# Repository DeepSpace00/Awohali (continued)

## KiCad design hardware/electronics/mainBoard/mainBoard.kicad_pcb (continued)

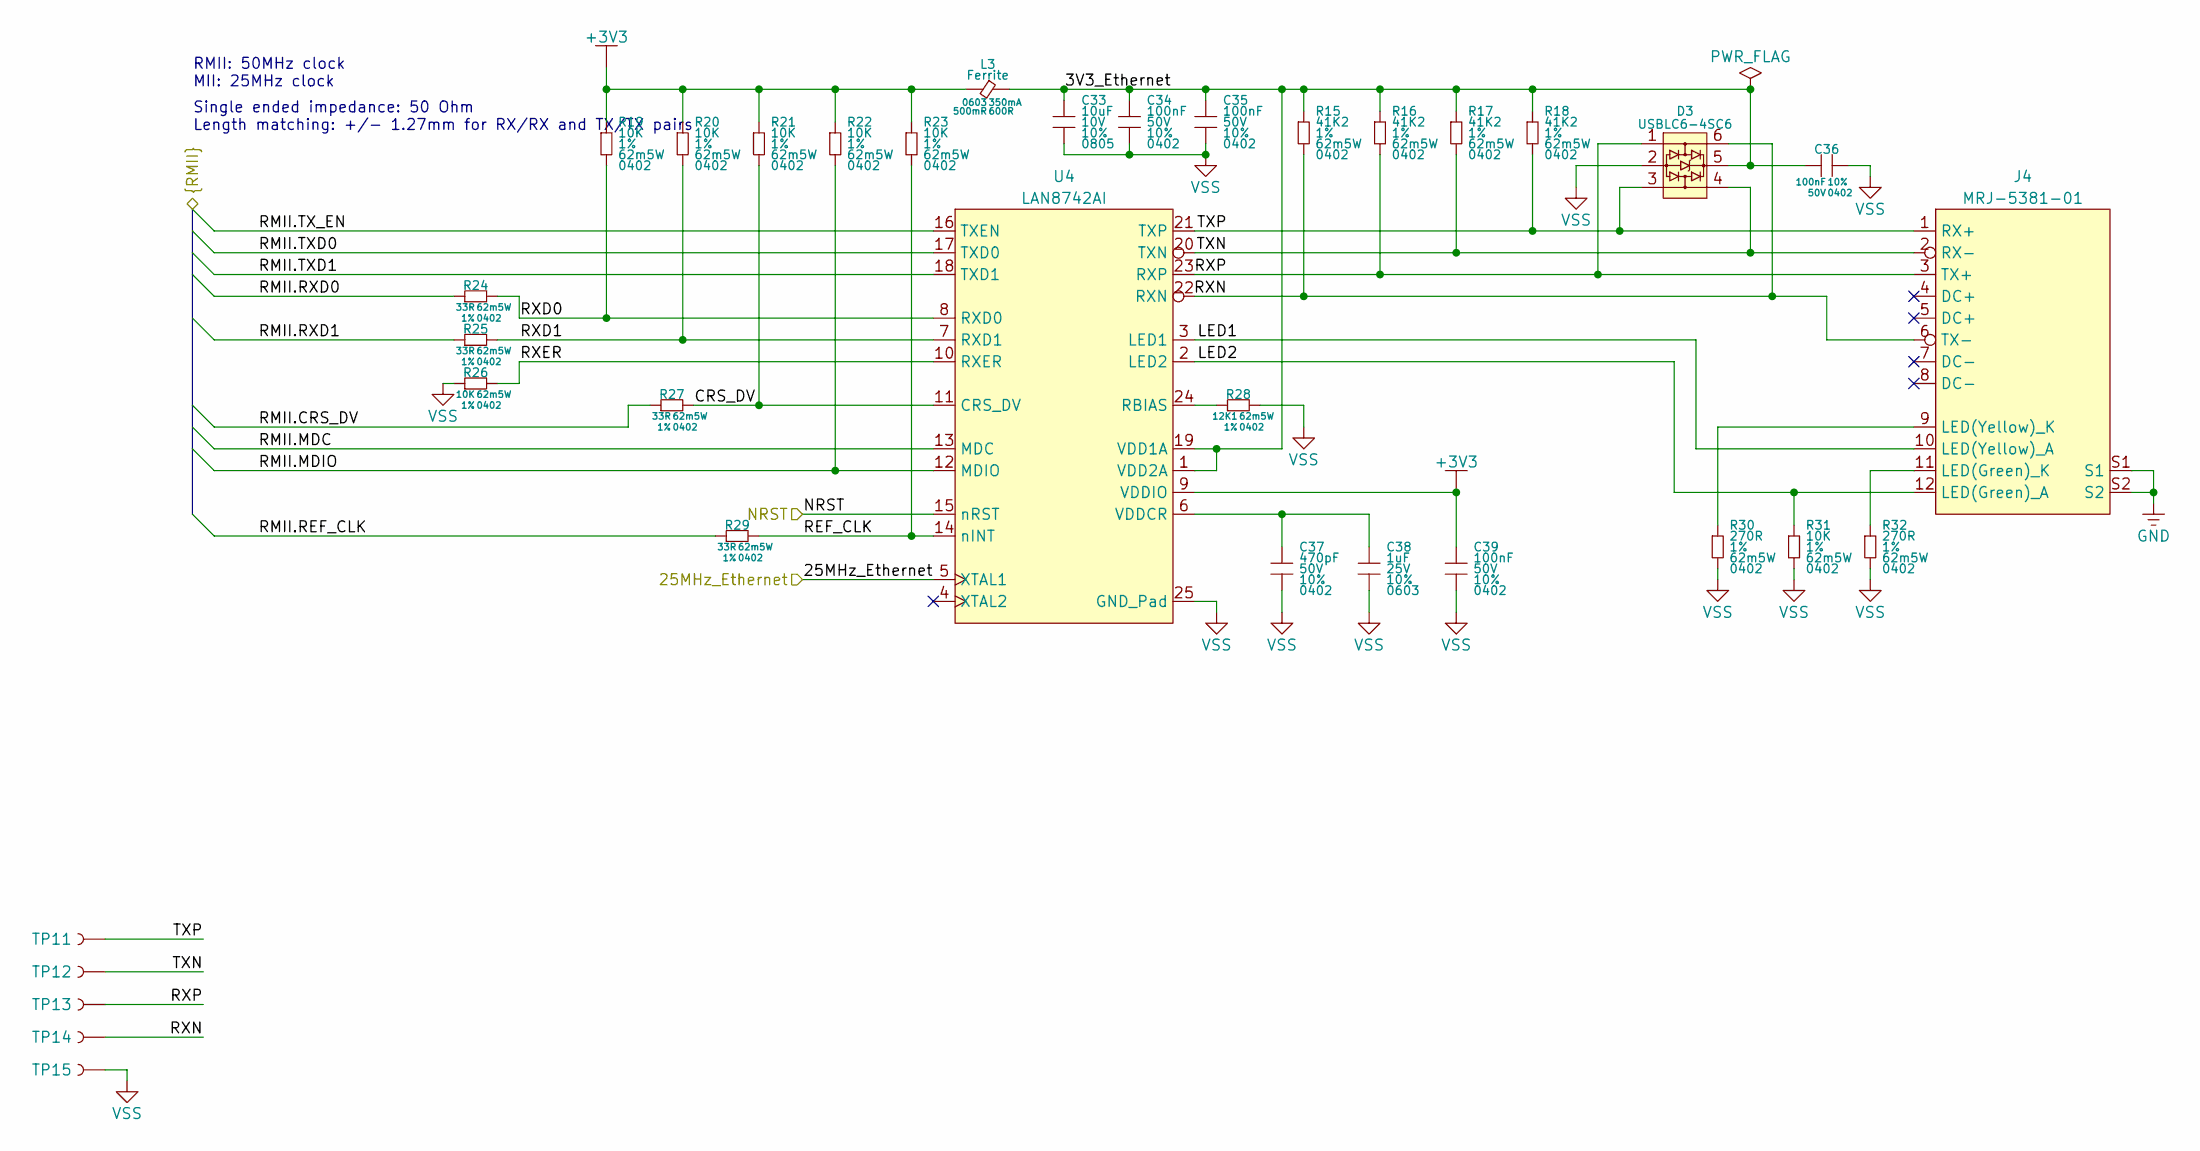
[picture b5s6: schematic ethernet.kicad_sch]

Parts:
C33: 10uF; GCM0805; Tolerance 10%; Voltage Rating 10V; MPN GCM21BR71A106KE22L
C34, C35, C36, C39: 100nF; GCM0402; Tolerance 10%; Voltage Rating 50V; MPN GRT155R71H104KE01D
C37: 470pF; GCM0402; Tolerance 10%; Voltage Rating 50V; MPN GRT155R71H471KE01D
C38: 1uF; GRT0603; Tolerance 10%; Voltage Rating 25V; MPN GRT188R71E105KE13D
D3: USBLC6-4SC6; SOT2395P280X145-6; MPN USBLC6-4SC6
J4: MRJ-5381-01; MJR-5381-X1; MPN MRJ-5381-01
L3: Ferrite; L_0603; Current Rating 350mA; MPN MFBA3V1608K-601-R
R15, R16, R17, R18: 41K2; CRCW0402; Tolerance 1%; Power Rating 62m5W; MPN CRCW040241R2FKED
R19, R20, R21, R22, R23, R26, R31: 10K; CRCW0402; Tolerance 1%; Power Rating 62m5W; MPN CRCW040210K0FKED
R24, R25, R27, R29: 33R; CRCW0402; Tolerance 1%; Power Rating 62m5W; MPN CRCW040233R0FKED
R28: 12K1; CRCW0402; Tolerance 1%; Power Rating 62m5W; MPN CRCW040212K1FKED
R30, R32: 270R; CRCW0402; Tolerance 1%; Power Rating 62m5W; MPN CRCW0402270RFKED
TP11, TP12, TP13, TP14: TP_2mm; MPN N/A
TP15: RCWCTE; TP_RCW; MPN RCWCTE
U4: LAN8742AI; QFN50P400X400X90-24; MPN LAN8742AI-CZ-TR

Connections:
+3V3: C39.1, L3.1, R19.1, R20.1, R21.1, R22.1, R23.1, U4.9 (VDDIO); also elsewhere on the board
/Ethernet/3V3_Ethernet: C33.1, C34.1, C35.1, C36.1, D3.5 (VBUS), L3.2, R15.1, R16.1, R17.1, R18.1, U4.1 (VDD2A), U4.19 (VDD1A)
/Ethernet/25MHz_Ethernet: U4.5 (XTAL1); also elsewhere on the board
/Ethernet/CRS_DV: R21.2, R27.2, U4.11 (CRS_DV)
/Ethernet/LED1: J4.10 (LED(Yellow)_A), U4.3 (LED1)
/Ethernet/LED2: J4.12 (LED(Green)_A), R31.1, U4.2 (LED2)
/Ethernet/REF_CLK: R23.2, R29.2, U4.14 (nINT)
/Ethernet/RMII.CRS_DV: R27.1; also elsewhere on the board
/Ethernet/RMII.MDC: U4.13 (MDC); also elsewhere on the board
/Ethernet/RMII.MDIO: R22.2, U4.12 (MDIO); also elsewhere on the board
/Ethernet/RMII.REF_CLK: R29.1; also elsewhere on the board
/Ethernet/RMII.RXD0: R24.1; also elsewhere on the board
/Ethernet/RMII.RXD1: R25.1; also elsewhere on the board
/Ethernet/RMII.TXD0: U4.17 (TXD0); also elsewhere on the board
/Ethernet/RMII.TXD1: U4.18 (TXD1); also elsewhere on the board
/Ethernet/RMII.TX_EN: U4.16 (TXEN); also elsewhere on the board
/Ethernet/RXD0: R19.2, R24.2, U4.8 (RXD0)
/Ethernet/RXD1: R20.2, R25.2, U4.7 (RXD1)
/Ethernet/RXER: R26.2, U4.10 (RXER)
/Ethernet/RXN: D3.6 (OUT1), J4.6 (TX-), R15.2, TP14.1, U4.22 (RXN)
/Ethernet/RXP: D3.1 (IN1), J4.3 (TX+), R16.2, TP13.1, U4.23 (RXP)
/Ethernet/TXN: D3.4 (OUT2), J4.2 (RX-), R17.2, TP12.1, U4.20 (TXN)
/Ethernet/TXP: D3.3 (IN2), J4.1 (RX+), R18.2, TP11.1, U4.21 (TXP)
/H7_NRST: U4.15 (nRST); also elsewhere on the board
GND: J4.S1, J4.S2; also elsewhere on the board
unnamed: J4.11 (LED(Green)_K), R32.1
unnamed: J4.9 (LED(Yellow)_K), R30.1
unnamed: R28.1, U4.24 (RBIAS)
unnamed: C37.1, C38.1, U4.6 (VDDCR)
VSS: C33.2, C34.2, C35.2, C36.2, C37.2, C38.2, C39.2, D3.2 (GND), R26.1, R28.2, R30.2, R31.2, R32.2, TP15.1, U4.25 (GND_Pad); also elsewhere on the board

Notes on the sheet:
RMII: 50MHz clock MII: 25MHz clock
Single ended impedance: 50 Ohm Length matching: +/- 1.27mm for RX/RX and TX/TX pairs

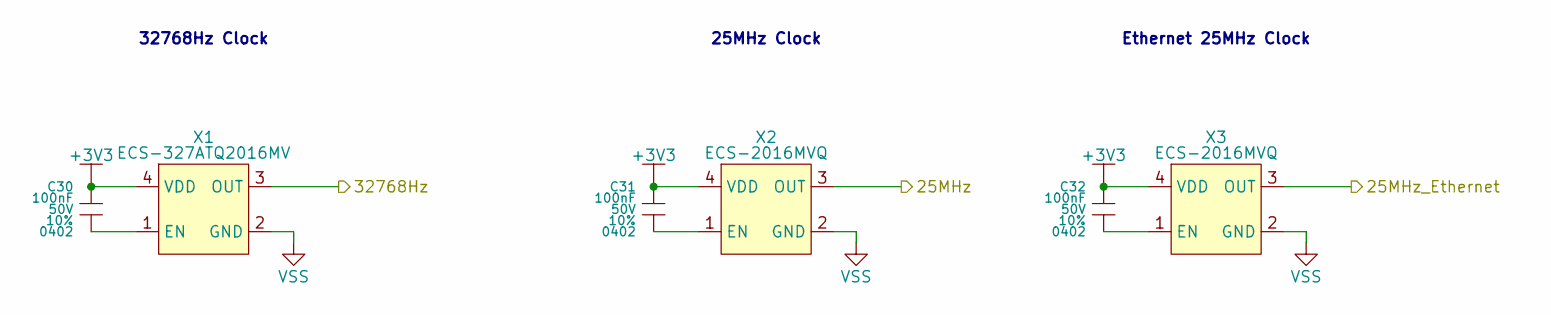
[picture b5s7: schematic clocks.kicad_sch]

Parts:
C30, C31, C32: 100nF; GCM0402; Tolerance 10%; Voltage Rating 50V; MPN GRT155R71H104KE01D
X1: ECS-327ATQ2016MV; ECS-xxxATQ2016MV; MPN ECS-327ATQ2016MV-BS-TR
X2, X3: ECS-2016MVQ; ECS-2016MV; MPN ECS-2016MVQ-250-CN-TR

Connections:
+3V3: C30.1, C31.1, C32.1, X1.4 (VDD), X2.4 (VDD), X3.4 (VDD); also elsewhere on the board
/Ethernet/25MHz_Ethernet: X3.3 (OUT); also elsewhere on the board
/STM32H745/25MHz: X2.3 (OUT); also elsewhere on the board
/STM32H745/32768Hz: X1.3 (OUT); also elsewhere on the board
unnamed: C30.2, X1.1 (EN)
unnamed: C31.2, X2.1 (EN)
unnamed: C32.2, X3.1 (EN)
VSS: X1.2 (GND), X2.2 (GND), X3.2 (GND); also elsewhere on the board

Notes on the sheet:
25MHz Clock
32768Hz Clock
Ethernet 25MHz Clock

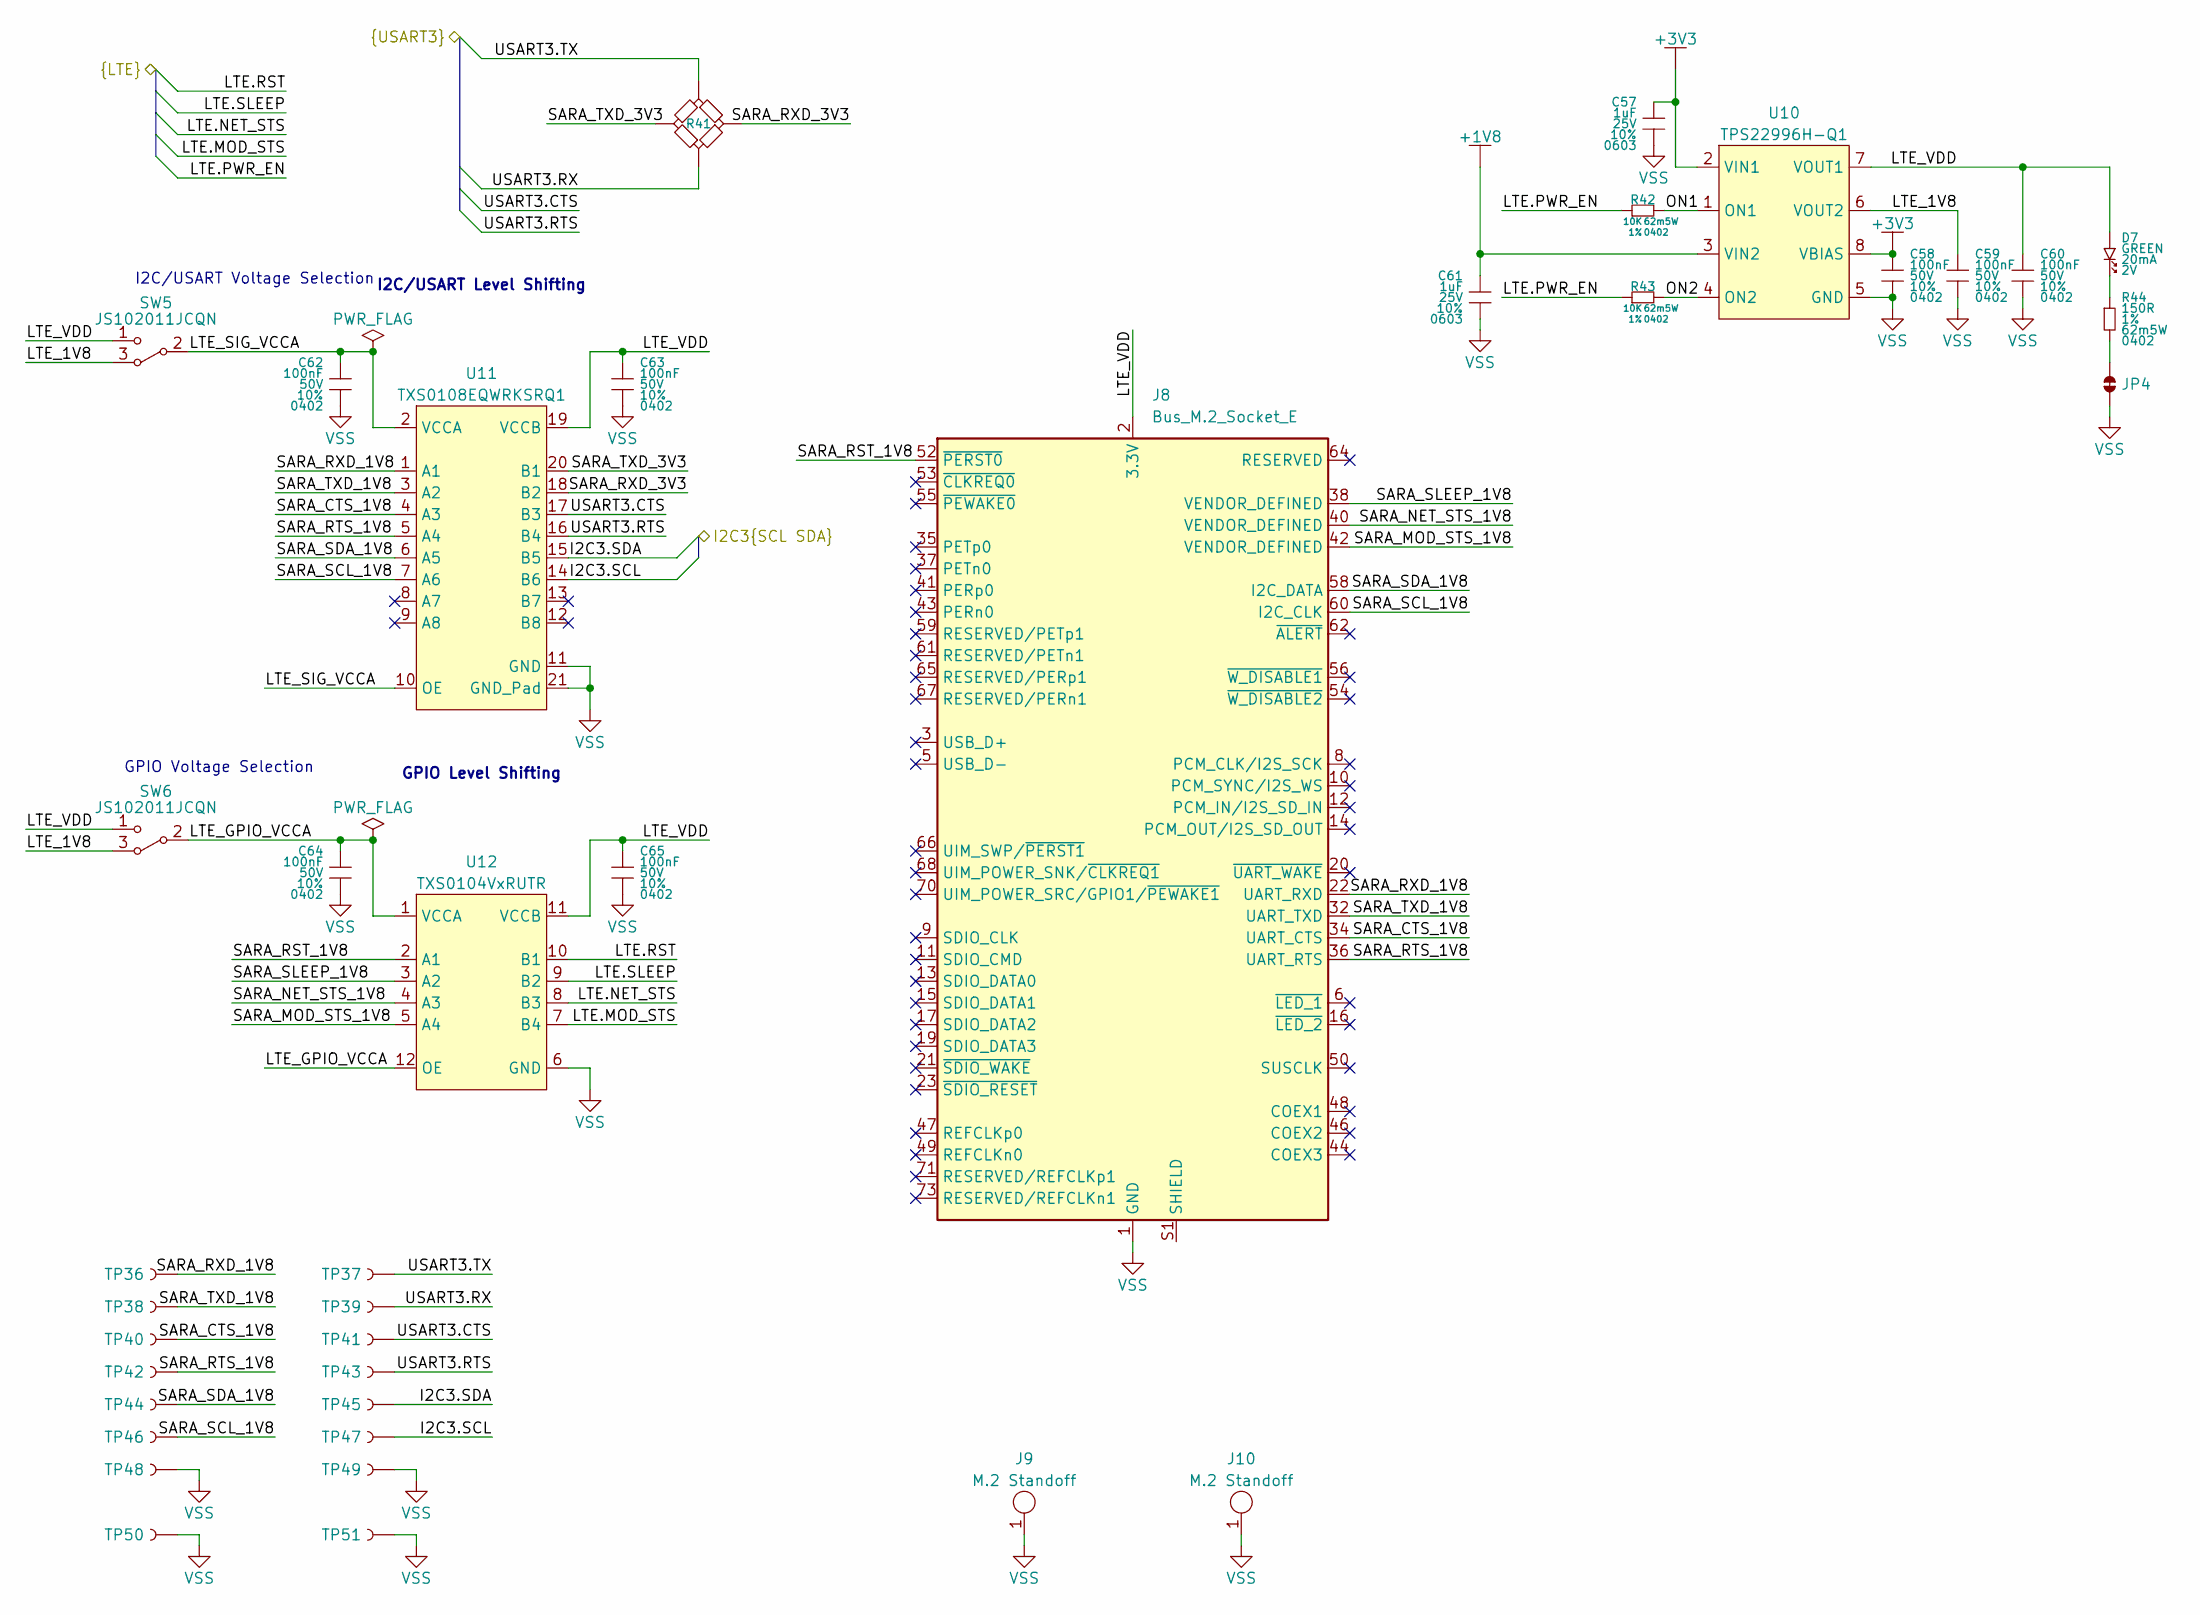
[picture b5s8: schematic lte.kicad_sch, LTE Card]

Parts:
C57, C61: 1uF; GRT0603; Tolerance 10%; Voltage Rating 25V; MPN GRT188R71E105KE13D
C58, C59, C60, C62, C63, C64, C65: 100nF; GCM0402; Tolerance 10%; Voltage Rating 50V; MPN GRT155R71H104KE01D
D7: LTST-C191KGKT; LTST-0603; Forward Voltage 2V; MPN LTST-C191KGKT
J8: Bus_M.2_Socket_E; MDT420E01001; MPN MDT420E01001
J9, J10: M.2 Standoff; MountingHole_3.5mm_Pad_Via; MPN 123A-NUT-42
JP4: SolderJumper-2_P1.3mm_Bridged_RoundedPad1.0x1.5mm
R41: CRCW0402_QUAD_UART
R42, R43: 10K; CRCW0402; Tolerance 1%; Power Rating 62m5W; MPN CRCW040210K0FKED
R44: 150R; CRCW0402; Tolerance 1%; Power Rating 62m5W; MPN CRCW0402150RFKED
SW5, SW6: JS102011JCQN; MPN C&K
TP36, TP37, TP38, TP39, TP40, TP41, TP42, TP43, TP44, TP45, TP46, TP47: TP_2mm; MPN N/A
TP48, TP49, TP50, TP51: RCWCTE; TP_RCW; MPN RCWCTE
U10: TPS22996H-Q1; SOT583; MPN TPS22996HQDYCRQ1
U11: TXS0108EQWRKSRQ1; QFN50P450X250X100-20; MPN TXS0108EQWRKSRQ1
U12: TXS0104VxRUTR; QFN40P170X200X55-12; MPN TXS0104VQRUTRQ1

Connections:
+1V8: C61.1, U10.3 (VIN2); also elsewhere on the board
+3V3: C57.1, C58.1, U10.2 (VIN1), U10.8 (VBIAS); also elsewhere on the board
/I2C3.SCL: TP47.1, U11.14 (B6); also elsewhere on the board
/I2C3.SDA: TP45.1, U11.15 (B5); also elsewhere on the board
/LTE Card/LTE.MOD_STS: U12.7 (B4); also elsewhere on the board
/LTE Card/LTE.NET_STS: U12.8 (B3); also elsewhere on the board
/LTE Card/LTE.PWR_EN: R42.1, R43.1; also elsewhere on the board
/LTE Card/LTE.RST: U12.10 (B1); also elsewhere on the board
/LTE Card/LTE.SLEEP: U12.9 (B2); also elsewhere on the board
/LTE Card/LTE_1V8: C59.1, SW5.3, SW6.3, U10.6 (VOUT2)
/LTE Card/LTE_GPIO_VCCA: C64.1, SW6.2, U12.1 (VCCA), U12.12 (OE)
/LTE Card/LTE_SIG_VCCA: C62.1, SW5.2, U11.2 (VCCA), U11.10 (OE)
/LTE Card/LTE_VDD: C60.1, C63.1, C65.1, D7.1, J8.2 (3.3V), J8.4 (3.3V), J8.72 (3.3V), J8.74 (3.3V), SW5.1, SW6.1, U10.7 (VOUT1), U11.19 (VCCB), U12.11 (VCCB)
/LTE Card/ON1: R42.2, U10.1 (ON1)
/LTE Card/ON2: R43.2, U10.4 (ON2)
/LTE Card/SARA_CTS_1V8: J8.34 (UART_CTS), TP40.1, U11.4 (A3)
/LTE Card/SARA_MOD_STS_1V8: J8.42 (VENDOR_DEFINED), U12.5 (A4)
/LTE Card/SARA_NET_STS_1V8: J8.40 (VENDOR_DEFINED), U12.4 (A3)
/LTE Card/SARA_RST_1V8: J8.52 (~PERST0), U12.2 (A1)
/LTE Card/SARA_RTS_1V8: J8.36 (UART_RTS), TP42.1, U11.5 (A4)
/LTE Card/SARA_RXD_1V8: J8.22 (UART_RXD), TP36.1, U11.1 (A1)
/LTE Card/SARA_RXD_3V3: R41.2, U11.18 (B2)
/LTE Card/SARA_SCL_1V8: J8.60 (I2C_CLK), TP46.1, U11.7 (A6)
/LTE Card/SARA_SDA_1V8: J8.58 (I2C_DATA), TP44.1, U11.6 (A5)
/LTE Card/SARA_SLEEP_1V8: J8.38 (VENDOR_DEFINED), U12.3 (A2)
/LTE Card/SARA_TXD_1V8: J8.32 (UART_TXD), TP38.1, U11.3 (A2)
/LTE Card/SARA_TXD_3V3: R41.4, U11.20 (B1)
/LTE Card/USART3.CTS: TP41.1, U11.17 (B3); also elsewhere on the board
/LTE Card/USART3.RTS: TP43.1, U11.16 (B4); also elsewhere on the board
/LTE Card/USART3.RX: R41.3, TP39.1; also elsewhere on the board
/LTE Card/USART3.TX: R41.1, TP37.1; also elsewhere on the board
unnamed: D7.2, R44.1
unnamed: J8.S1 (SHIELD), J8.S2 (SHIELD)
unnamed: JP4.1, R44.2
VSS: C57.2, C58.2, C59.2, C60.2, C61.2, C62.2, C63.2, C64.2, C65.2, J8.1 (GND), J8.7 (GND), J8.18 (GND), J8.33 (GND), J8.39 (GND), J8.45 (GND), J8.51 (GND), J8.57 (GND), J8.63 (GND), J8.69 (GND), J8.75 (GND), J9.1, J10.1, JP4.2, TP48.1, TP49.1, TP50.1, TP51.1, U10.5 (GND), U11.11 (GND), U11.21 (GND_Pad), U12.6 (GND); also elsewhere on the board

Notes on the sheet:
I2C/USART Voltage Selection
I2C/USART Level Shifting
GPIO Voltage Selection
GPIO Level Shifting

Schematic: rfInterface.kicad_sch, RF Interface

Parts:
AE1: TNC; RFPC-TNC01-FN; MPN RFPC-TNC01-FN-A
AE2: SMA; RFPC-SMA14-FN; MPN RFPC-SMA14-FN-A
AE3: SMA; RFPC-SMA14-FN; MPN RFPC-SMA14-FN-A; not fitted
C75, C76: 100nF; GCM0402; Tolerance 10%; Voltage Rating 50V; MPN GRT155R71H104KE01D
C77, C79: 9.1pF; GCM0402; Tolerance 0.1pF; Voltage Rating 50V; MPN GCM1555C1H9R1BA16D
C78: 5.6pF; GCM0402; Tolerance 0.1pF; Voltage Rating 50V; MPN GCM1555C1H5R6BA16D
C80, C81: 100pF; GCM0402; Tolerance 1%; Voltage Rating 50V; MPN GCM1555C1H101FA16D
J14, J15, J16, J17: CONMHF1-SMD-T; CONMHF1; MPN CONMHF1-SMD-T
L4: 15nH; L_0402; Tolerance 2%; Current Rating 1A15; MPN LQW15AN15NG8ZD
L5: 6.8nH; L_0402; Tolerance 2%; Current Rating 1A45; MPN LQW15AN6N8G8ZD
R53: 750R; CRCW0402; Tolerance 1%; Power Rating 62m5W; MPN CRCW0402750RFKED
R54: 267R; CRCW0402; Tolerance 1%; Power Rating 62m5W; MPN CRCW0402267RFKED
R55: 49R9; CRCW0402; Tolerance 1%; Power Rating 62m5W; MPN CRCW040249R9FKED
U16: PMA2-162LNA+; TFDFN200X200X100-8; MPN PMA2-162LNA+
U17: QCN-19D+; SON99P320X160X89-6; MPN QCN-19D+

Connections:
/RF Interface/AUX_RF-IN: AE3.1 (A), J17.1 (In)
/RF Interface/GNSS_CONN1: J14.1 (In), U17.4 (PORT1)
/RF Interface/GNSS_CONN2: J15.1 (In), U17.6 (PORT2)
/RF Interface/GNSS_RF-IN: AE1.1 (A), C79.1
/RF Interface/LNA_BIAS: R53.2, U16.4 (BIAS)
/RF Interface/LNA_FB: C78.1, U16.5 (FB)
/RF Interface/LNA_RBIAS: C75.1, C76.1, C77.1, L4.1, R53.1
/RF Interface/LNA_RF-GND: C81.1, L5.2, U16.3 (RF-GND)
/RF Interface/LNA_RF-IN: C79.2, L5.1, U16.2 (RF-IN)
/RF Interface/LNA_RF-OUT: C80.1, L4.2, R54.2, U16.7 (RF-OUT)
/RF Interface/LTE_RF-IN: AE2.1 (A), J16.1 (In)
/RF Interface/RF-SPLIT_50R: R55.1, U17.3 (50R)
/RF Interface/RF-SPLIT_SUM: C80.2, U17.1 (SUM)
unnamed: C78.2, R54.1
VSS: AE1.2 (Shield), AE1.3 (Shield), AE1.4 (Shield), AE1.5 (Shield), AE2.2 (Shield), AE2.3 (Shield), AE2.4 (Shield), AE2.5 (Shield), AE3.2 (Shield), AE3.3 (Shield), AE3.4 (Shield), AE3.5 (Shield), C75.2, C76.2, C77.2, C81.2, J14.2 (Ext), J15.2 (Ext), J16.2 (Ext), J17.2 (Ext), R55.2, U16.1 (NC), U16.6 (NC), U16.8 (GND), U16.9 (GND), U17.2 (GND), U17.5 (GND); also elsewhere on the board

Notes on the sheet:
GNSS Card Cable
LTE Card Cable
Single ended impedance: 50 Ohms
AUX Card Cable

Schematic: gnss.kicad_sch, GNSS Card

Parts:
C48, C52: 1uF; GRT0603; Tolerance 10%; Voltage Rating 25V; MPN GRT188R71E105KE13D
C49, C50, C51, C53, C54, C55, C56: 100nF; GCM0402; Tolerance 10%; Voltage Rating 50V; MPN GRT155R71H104KE01D
D4: LTST-C191KGKT; LTST-0603; Forward Voltage 2V; MPN LTST-C191KGKT
J5: Bus_M.2_Socket_E; MDT420E01001; MPN MDT420E01001
J6, J7: M.2 Standoff; MountingHole_3.5mm_Pad_Via; MPN 123A-NUT-42
JP1: SolderJumper-2_P1.3mm_Bridged_RoundedPad1.0x1.5mm
R35: CRCW0402_QUAD_UART
R36, R37: 10K; CRCW0402; Tolerance 1%; Power Rating 62m5W; MPN CRCW040210K0FKED
R38: 150R; CRCW0402; Tolerance 1%; Power Rating 62m5W; MPN CRCW0402150RFKED
SW3, SW4: JS102011JCQN; MPN C&K
TP24, TP25, TP26, TP27, TP28, TP29, TP30, TP31: TP_2mm; MPN N/A
TP32, TP33, TP34, TP35: RCWCTE; TP_RCW; MPN RCWCTE
U7: TPS22996H-Q1; SOT583; MPN TPS22996HQDYCRQ1
U8, U9: TXS0104VxRUTR; QFN40P170X200X55-12; MPN TXS0104VQRUTRQ1

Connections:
+1V8: C52.1, U7.3 (VIN2); also elsewhere on the board
+3V3: C48.1, C49.1, U7.2 (VIN1), U7.8 (VBIAS); also elsewhere on the board
/GNSS Card/GNSS.INT: U9.9 (B2); also elsewhere on the board
/GNSS Card/GNSS.PPS: U9.10 (B1); also elsewhere on the board
/GNSS Card/GNSS.PWR_EN: R36.1, R37.1; also elsewhere on the board
/GNSS Card/GNSS.RST: J5.52 (~PERST0); also elsewhere on the board
/GNSS Card/GNSS.TX_RDY: U9.8 (B3); also elsewhere on the board
/GNSS Card/GNSS_1V8: C50.1, SW3.3, SW4.3, U7.6 (VOUT2)
/GNSS Card/GNSS_VDD: C51.1, C54.1, C56.1, D4.1, J5.2 (3.3V), J5.4 (3.3V), J5.72 (3.3V), J5.74 (3.3V), SW3.1, SW4.1, U7.7 (VOUT1), U8.11 (VCCB), U9.11 (VCCB)
/GNSS Card/GPS_GPIO_VCCA: C55.1, SW4.2, U9.1 (VCCA), U9.12 (OE)
/GNSS Card/GPS_SIG_VCCA: C53.1, SW3.2, U8.1 (VCCA), U8.12 (OE)
/GNSS Card/ON1: R36.2, U7.1 (ON1)
/GNSS Card/ON2: R37.2, U7.4 (ON2)
/GNSS Card/UART5.RX: R35.1, TP25.1; also elsewhere on the board
/GNSS Card/UART5.TX: R35.3, TP27.1; also elsewhere on the board
/GNSS Card/ZED_INT: J5.40 (VENDOR_DEFINED), U9.3 (A2)
/GNSS Card/ZED_PPS: J5.38 (VENDOR_DEFINED), U9.2 (A1)
/GNSS Card/ZED_RXD_1V8: J5.22 (UART_RXD), TP26.1, U8.3 (A2)
/GNSS Card/ZED_RXD_3V3: R35.2, U8.9 (B2)
/GNSS Card/ZED_SCL_1V8: J5.60 (I2C_CLK), TP30.1, U8.5 (A4)
/GNSS Card/ZED_SDA_1V8: J5.58 (I2C_DATA), TP28.1, U8.4 (A3)
/GNSS Card/ZED_TXD_1V8: J5.32 (UART_TXD), TP24.1, U8.2 (A1)
/GNSS Card/ZED_TXD_3V3: R35.4, U8.10 (B1)
/GNSS Card/ZED_TX_RDY: J5.42 (VENDOR_DEFINED), U9.4 (A3)
/I2C2.SCL: TP31.1, U8.7 (B4); also elsewhere on the board
/I2C2.SDA: TP29.1, U8.8 (B3); also elsewhere on the board
unnamed: D4.2, R38.1
unnamed: JP1.1, R38.2
VSS: C48.2, C49.2, C50.2, C51.2, C52.2, C53.2, C54.2, C55.2, C56.2, J5.1 (GND), J5.7 (GND), J5.18 (GND), J5.33 (GND), J5.39 (GND), J5.45 (GND), J5.51 (GND), J5.57 (GND), J5.63 (GND), J5.69 (GND), J5.75 (GND), J5.S1 (SHIELD), J5.S2 (SHIELD), J6.1, J7.1, JP1.2, TP32.1, TP33.1, TP34.1, TP35.1, U7.5 (GND), U8.6 (GND), U9.6 (GND); also elsewhere on the board

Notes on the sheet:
I2C/UART Voltage Selection
GPIO Level Shifting
GNSS Receiver GPIO
GPIO Voltage Selection
I2C/UART Level Shifting

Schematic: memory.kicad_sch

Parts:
C27, C28, C29: 100nF; GCM0402; Tolerance 10%; Voltage Rating 50V; MPN GRT155R71H104KE01D
J3: MEM2067-02-180-00-A; MPN MEM2067-02-180-00-A
TP1, TP2, TP3, TP4, TP5, TP6, TP7, TP8: TP_2mm; MPN N/A
TP9, TP10: RCWCTE; TP_RCW; MPN RCWCTE
U2: W25Q128JVP; WFDFN8P127_600X500X75L60X40N; MPN W25Q128JVPIQ
U3: M24512-DRE; SOIC127P600x175-8; MPN M24512-DRMN8TP/K

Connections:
+3V3: C27.1, C28.1, C29.1, J3.4 (VDD), U2.8 (VCC), U3.8 (VCC); also elsewhere on the board
/I2C1.SCL: TP1.1, U3.6 (SCL); also elsewhere on the board
/I2C1.SDA: TP2.1, U3.5 (SDA); also elsewhere on the board
/Memory/EEPROM_WC: U3.7 (~WC); also elsewhere on the board
/Memory/QSPI1.CLK: TP4.1, U2.6 (SCK); also elsewhere on the board
/Memory/QSPI1.IO0: TP5.1, U2.5 (IO0); also elsewhere on the board
/Memory/QSPI1.IO1: TP6.1, U2.2 (IO1); also elsewhere on the board
/Memory/QSPI1.IO2: TP7.1, U2.3 (IO2); also elsewhere on the board
/Memory/QSPI1.IO3: TP8.1, U2.7 (IO3); also elsewhere on the board
/Memory/QSPI1.NCS: TP3.1, U2.1 (~CS); also elsewhere on the board
/Memory/SDMMC2.CLK: J3.5 (CLK); also elsewhere on the board
/Memory/SDMMC2.CMD: J3.3 (CMD); also elsewhere on the board
/Memory/SDMMC2.D0: J3.7 (DAT0); also elsewhere on the board
/Memory/SDMMC2.D1: J3.8 (DAT1); also elsewhere on the board
/Memory/SDMMC2.D2: J3.1 (DAT2); also elsewhere on the board
/Memory/SDMMC2.D3: J3.2 (DAT3/CD); also elsewhere on the board
VSS: C27.2, C28.2, C29.2, J3.6 (VSS), J3.S1 (SHIELD), J3.S2 (SHIELD), J3.S3 (SHIELD), J3.S4 (SHIELD), TP9.1, TP10.1, U2.4 (GND), U2.9 (GND_PAD), U3.1 (E0), U3.2 (E1), U3.3 (E2), U3.4 (VSS); also elsewhere on the board

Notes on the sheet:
I2C Address: 0x50/0x58

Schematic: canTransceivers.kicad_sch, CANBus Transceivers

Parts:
C40, C41, C44, C45: 1uF; GRT0603; Tolerance 10%; Voltage Rating 25V; MPN GRT188R71E105KE13D
C42, C43, C46, C47: 100nF; GCM0402; Tolerance 10%; Voltage Rating 50V; MPN GRT155R71H104KE01D
R33, R34: 120R; CRCW0402; Tolerance 1%; Power Rating 62m5W; MPN CRCW0402120RFKED
TP16, TP17, TP18, TP19, TP20, TP21: TP_2mm; MPN N/A
TP22, TP23: RCWCTE; TP_RCW; MPN RCWCTE
U5, U6: TCAN3403-Q1; SON65P300X300X100-8; MPN TCAN3403DRBRQ1

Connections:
+3V3: C40.1, C41.1, C42.1, C43.1, C44.1, C45.1, C46.1, C47.1, U5.3 (VCC), U5.5 (VDDIO), U6.3 (VCC), U6.5 (VDDIO); also elsewhere on the board
/CANBus Transceivers/CANH: R33.1, R34.1, TP18.1, U5.7 (CANH), U6.7 (CANH)
/CANBus Transceivers/CANL: R33.2, R34.2, TP19.1, U5.6 (CANL), U6.6 (CANL)
/CANBus Transceivers/FDCAN1_RX: TP17.1, U5.4 (RXD); also elsewhere on the board
/CANBus Transceivers/FDCAN1_TX: TP16.1, U5.1 (TXD); also elsewhere on the board
/CANBus Transceivers/H7_CAN_STB: U5.8 (STB); also elsewhere on the board
/CAN_RXD: TP21.1, U6.4 (RXD); also elsewhere on the board
/CAN_STB: U6.8 (STB); also elsewhere on the board
/CAN_TXD: TP20.1, U6.1 (TXD); also elsewhere on the board
VSS: C40.2, C41.2, C42.2, C43.2, C44.2, C45.2, C46.2, C47.2, TP22.1, TP23.1, U5.2 (GND), U5.9 (GND_PAD), U6.2 (GND), U6.9 (GND_PAD); also elsewhere on the board

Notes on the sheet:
EPS CANBus Transceiver
Host CANBus Transceiver

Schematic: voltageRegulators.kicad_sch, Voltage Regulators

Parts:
C124, C130: 100nF; GCM0402; Tolerance 10%; Voltage Rating 50V; MPN GRT155R71H104KE01D
C125: 4.7uF; GCM0805; Tolerance 10%; Voltage Rating 16V; MPN GRT21BR71C475KE13L
C126, C127, C128, C134: 22uF; GCM1206; Tolerance 20%; Voltage Rating 10V; MPN GCM31CR71A226ME02L
C129: 2.2uF; GCM0805; Tolerance 10%; Voltage Rating 25V; MPN GRT21BR71E225KE13L
C131: 150pF; GCM0402; Tolerance 1%; Voltage Rating 50V; MPN GCM1555C1H151FA16J
C132: 3.9nF; GCM0402; Tolerance 10%; Voltage Rating 50V; MPN GCM155R71H392KA37D
C133: 10uF; GCM0805; Tolerance 10%; Voltage Rating 10V; MPN GCM21BR71A106KE22L
D21, D22: LTST-C191KRKT; LTST-0603; Forward Voltage 2V; MPN LTST-C191KRKT
J30, J31: Conn_01x04_Pin; conn_01x04_254; MPN PRPC004SAAN-RC
JP11, JP13: SolderJumper-2_P1.3mm_Bridged_RoundedPad1.0x1.5mm
JP12: SolderJumper-3_P1.3mm_Bridged12_RoundedPad1.0x1.5mm
L7: 6.8uH; WE-XHMI-1090; Tolerance 20%; Current Rating 10A5; MPN 74439369068
L8: 1uH; WE-XHMI-8080; Tolerance 20%; Current Rating 17A; MPN 74439358010
Q8, Q9: CSD17581Q3A; SON65P300X315X90-8; MPN CSD17581Q3A
Q10, Q11: BSS138-7-F; SOT23; MPN BSS138-7-F
R83, R90: 150R; CRCW0402; Tolerance 1%; Power Rating 62m5W; MPN CRCW0402150RFKED
R84, R91: 0R; CRCW1210; Tolerance N/A; Power Rating 500mW; MPN CRCW12100000Z0EA; not fitted
R85: 25mR; CRCW0805; Tolerance 1%; Power Rating 500mW; MPN WSLP0805R0250FEB
R86, R94: 100K; CRCW0402; Tolerance 1%; Power Rating 62m5W; MPN CRCW0402100KFKED
R87: 53.6k; CRCW0402; Tolerance 1%; Power Rating 62m5W; MPN CRCW040253K6FKED
R88: 5k11; CRCW0402; Tolerance 1%; Power Rating 62m5W; MPN CRCW04025K11FKED
R89: 41K2; CRCW0402; Tolerance 1%; Power Rating 62m5W; MPN CRCW040241R2FKED
R92: 200K; CRCW0402; Tolerance 1%; Power Rating 62m5W; MPN CRCW0402200KFKED
R93: 499K; CRCW0402; Tolerance 1%; Power Rating 62m5W; MPN CRCW0402499KFKED
TP95, TP96, TP97, TP98: TP_2mm; MPN N/A
TP99, TP100: RCWCTE; TP_RCW; MPN RCWCTE
U22: LM25148-Q1; QFN50P350X550X100-24; MPN LM25148BQRGYRQ1
U23: TPS62A01; SOT563; MPN TPS62A01DRLR

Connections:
+1V8: J31.3, R91.1, TP96.1; also elsewhere on the board
+3V3: C133.1, J30.3, R83.1, R84.1, R86.1, R90.1, R93.1, TP95.1, U23.3 (VIN); also elsewhere on the board
/EPS Controller/EN_1V8: U23.4 (EN); also elsewhere on the board
/EPS Controller/PG_1V8: Q11.1, R93.2, TP98.1, U23.6 (PG); also elsewhere on the board
/EPS Controller/PG_3V3: Q10.1, R86.2, TP97.1, U22.17 (PG); also elsewhere on the board
/EPS Controller/Voltage Regulators/CBOOT: C124.1, U22.15 (CBOOT)
/EPS Controller/Voltage Regulators/FB_1V8: R92.2, R94.1, U23.5 (FB)
/EPS Controller/Voltage Regulators/HO: Q8.4, U22.13 (HO)
/EPS Controller/Voltage Regulators/ISNS+: L7.2, R85.1, U22.20 (ISNS+)
/EPS Controller/Voltage Regulators/LO: Q9.4, U22.11 (LO)
/EPS Controller/Voltage Regulators/PFM: JP12.2 (C), U22.18 (PFM)
/EPS Controller/Voltage Regulators/RT: R87.1, U22.4 (RT)
/EPS Controller/Voltage Regulators/SW: C124.2, L7.1, Q8.1, Q8.2, Q8.3, Q9.5, Q9.6, Q9.7, Q9.8, Q9.9, U22.14 (SW)
/EPS Controller/Voltage Regulators/SW_1V8: L8.1, U23.2 (SW)
/EPS Controller/Voltage Regulators/VDDA: C130.1, JP12.1 (A), U22.6 (FB), U22.8 (VDDA)
AGND: C130.2, C131.2, C132.2, JP12.3 (B), R87.2, R89.2, TP100.1, U22.7 (AGND); also elsewhere on the board
GND: C125.2, C126.2, C127.2, C128.2, C129.2, C133.2, C134.2, J30.1, J30.4, J31.1, J31.4, JP11.2, JP13.2, Q9.1, Q9.2, Q9.3, R94.2, TP99.1, U22.1 (NC), U22.2 (NC), U22.10 (PGND), U22.16 (VCCX), U22.22 (NC), U22.23 (NC), U22.24 (NC), U22.25 (EP), U23.1 (GND); also elsewhere on the board
unnamed: C132.1, R88.2
unnamed: D21.1, R83.2
unnamed: D21.2, Q10.3
unnamed: D22.1, R90.2
unnamed: D22.2, Q11.3
unnamed: C126.1, C127.1, C128.1, J30.2, R84.2, R85.2, U22.21 (VOUT)
unnamed: C134.1, J31.2, L8.2, R91.2, R92.1
unnamed: JP11.1, Q10.2
unnamed: JP13.1, Q11.2
unnamed: R89.1, U22.3 (CNFG)
unnamed: C131.1, R88.1, U22.5 (EXTCOMP)
unnamed: C129.1, U22.9 (VCC)
VSYS: C125.1, Q8.5, Q8.6, Q8.7, Q8.8, Q8.9, U22.12 (VIN), U22.19 (EN); also elsewhere on the board

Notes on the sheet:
Connect FB to VDDA for Vout=3V3
PWM/FPWM Selection PWM mode default
+1V8 Voltage Regulator @ 100-250mA
Nordic PPK Connector for current measurement
Passes PSPICE sim w/ Vout_ripple ~= 3.6mV @ 100mA load & ~1.7mV @ 250mA load
+3V3 Voltage Regulator @ 0.5-1.75A & 406kHz
R1 = R2 * (Vout/0.6V - 1) Vout = 1V8 R2 = 100k R1 = 200k
Passes PSPICE sim w/ Vout_ripple ~= 10mV @ 500mA load & ~5mV @ 1.5A load

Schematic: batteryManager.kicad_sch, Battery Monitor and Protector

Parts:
C111, C112, C113: 220nF; GCM0402; Voltage Rating 16V; Tolerance 10%; MPN GRT155R71C224KE01D
C114, C116: 2.2uF; GCM0805; Tolerance 10%; Voltage Rating 25V; MPN GRT21BR71E225KE13L
C115, C119: 100pF; GCM0402; Tolerance 1%; Voltage Rating 50V; MPN GCM1555C1H101FA16D
C117: 1uF; GRT0603; Voltage Rating 25V; Tolerance 10%; MPN GRT188R71E105KE13D
C118, C120, C121: 100nF; GCM0402; Tolerance 10%; Voltage Rating 50V; MPN GRT155R71H104KE01D
C122, C123: 100nF; GCM0402; Voltage Rating 50V; Tolerance 10%; MPN GRT155R71H104KE01D
D18, D19: SDM20U40Q-7; SOD523; Reverse Voltage 40V; Forward Voltage 600mV; MPN SDM20U40Q-7
D20: MMSZ5246B-7-F; SOD123; Zener Voltage 16V; Forward Voltage 900mV; MPN MMSZ5246B-7-F
J28: S3B-XH-SM4-TB; JST_XH_S3B-SM4-TB; MPN S3B-XH-SM4-TB
J29: 1726480102; MPN 1726480102
NT9, NT10, NT11: NetTie; NetTie-2_SMD_Pad2.0mm
Q6, Q7: BUK6D72-30EX; UDFN6P65_200X200X65L30X25N; MPN BUK6D72-30EX
R73, R74, R75: 10R; CRCW2010; Tolerance 1%; Power Rating 750mW; MPN CRCW201010R0FKEF
R76, R77, R81: 100R; CRCW0402; Tolerance 5%; Power Rating 62m5W; MPN CRCW0402100RJNED
R78, R79: 5K1; CRCW0402; Tolerance 1%; Power Rating 62m5W; MPN CRCW04025K10FKED
R80: 25mR; WSL2512-HP; Tolerance 1%; Power Rating 2W; MPN WSL2512R0400FEA18
R82: 10M; CRCW0402; Tolerance 1%; Power Rating 62m5W; MPN CRCW040210M0FKED
TP91, TP92: TP_2mm; MPN N/A
TP93, TP94: RCWCTE; TP_RCW; MPN RCWCTE
U21: BQ76905; QFN50P350X350X100-20; MPN BQ76905RGRR

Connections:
/EPS Controller/BAL_ALERT: U21.14 (ALERT); also elsewhere on the board
/EPS Controller/Battery Manager/1P: J28.2, R74.1, TP92.1
/EPS Controller/Battery Manager/CHG: R79.1, U21.10 (CHG)
/EPS Controller/Battery Manager/CHG_G: D20.2, Q7.3, R79.2, R82.1
/EPS Controller/Battery Manager/DSG: R78.1, U21.9 (DSG)
/EPS Controller/Battery Manager/DSG_G: Q6.3, R78.2
/EPS Controller/Battery Manager/DSG_S: C122.1, Q6.4, Q6.8, R80.2, R81.1
/EPS Controller/Battery Manager/REGOUT: C116.1, U21.15 (REGOUT)
/EPS Controller/Battery Manager/REGSRC: C117.1, D18.1, U21.16 (REGSRC)
/EPS Controller/Battery Manager/SRN: C118.2, C119.2, R81.2, U21.7 (SRN)
/EPS Controller/Battery Manager/SRP: C118.1, C119.1, R77.2, U21.6 (SRP)
/EPS Controller/Battery Manager/VC0: C112.2, C113.1, R75.2, U21.5 (VC0)
/EPS Controller/Battery Manager/VC1: C111.2, C112.1, R74.2, U21.1 (VC3A), U21.2 (VC3B), U21.3 (VC2), U21.4 (VC1), U21.19 (VC4A), U21.20 (VC4B)
/EPS Controller/Battery Manager/VC5: C111.1, R73.2, U21.18 (VC5)
/EPS Controller/TS: U21.8 (TS); also elsewhere on the board
/EPS.SCL: U21.12 (SCL); also elsewhere on the board
/EPS.SDA: U21.13 (SDA); also elsewhere on the board
CHG+: C120.1, NT10.1; also elsewhere on the board
CHG-: C121.2, C123.2, D20.1, NT11.1, Q7.4, Q7.8, R82.2; also elsewhere on the board
GND: C113.2, C114.2, C115.2, NT9.1, NT11.2, TP94.1, U21.11 (VSS), U21.21 (PGND); also elsewhere on the board
unnamed: C116.2, C117.2
unnamed: C120.2, C121.1
unnamed: C122.2, C123.1
unnamed: D19.1, R76.1
unnamed: Q6.1, Q6.2, Q6.5, Q6.6, Q6.7, Q7.1, Q7.2, Q7.5, Q7.6, Q7.7
unnamed: C114.1, C115.1, R76.2, U21.17 (BAT)
PACK+: D18.2, D19.2, J28.1, J29.1, NT10.2, R73.1, TP91.1
PACK-: J28.3, J29.2, NT9.2, R75.1, R77.1, R80.1, TP93.1

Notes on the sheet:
MaxAmps LFP-Max LiFePO4 5000 2S 6.6V Battery Pack Balance Connector
I2C Address: 0x10/0x11
Mates with: Molex MiniFit Sigma 2004531002 (use 16 AWG) Molex MiniFit Jr. 469940212 (use 16 AWG)
